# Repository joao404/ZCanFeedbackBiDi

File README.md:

# ZCanFeedbackBiDi
This project is based on the work of:
- Philipp Gathow (https://pgahtow.de/w/R%C3%BCckmeldung 8xRailCom-Detektor)
- Zimo Can Protocol

Several projects are include:
- Roco/Zimo CAN protocol to Z21 ethernet interface converter on ESP32
- Roco 10808 compatible Bidi/Railcom detector on ESP32 (currently suspended)
- Roco 10808 compatible Bidi/Railcom detector on STM32 using STM32Cube (currently suspended)
- Roco 10808 compatible Bidi/Railcom detector on STM32 using Arduino framework (ongoing. Planned to be finished on winter 2023)
- Roco 10808 compatible Bidi/Railcom detector on STM32 using Arduino framework and FreeRtos (ongoing. Planned to be finished on winter 2023)

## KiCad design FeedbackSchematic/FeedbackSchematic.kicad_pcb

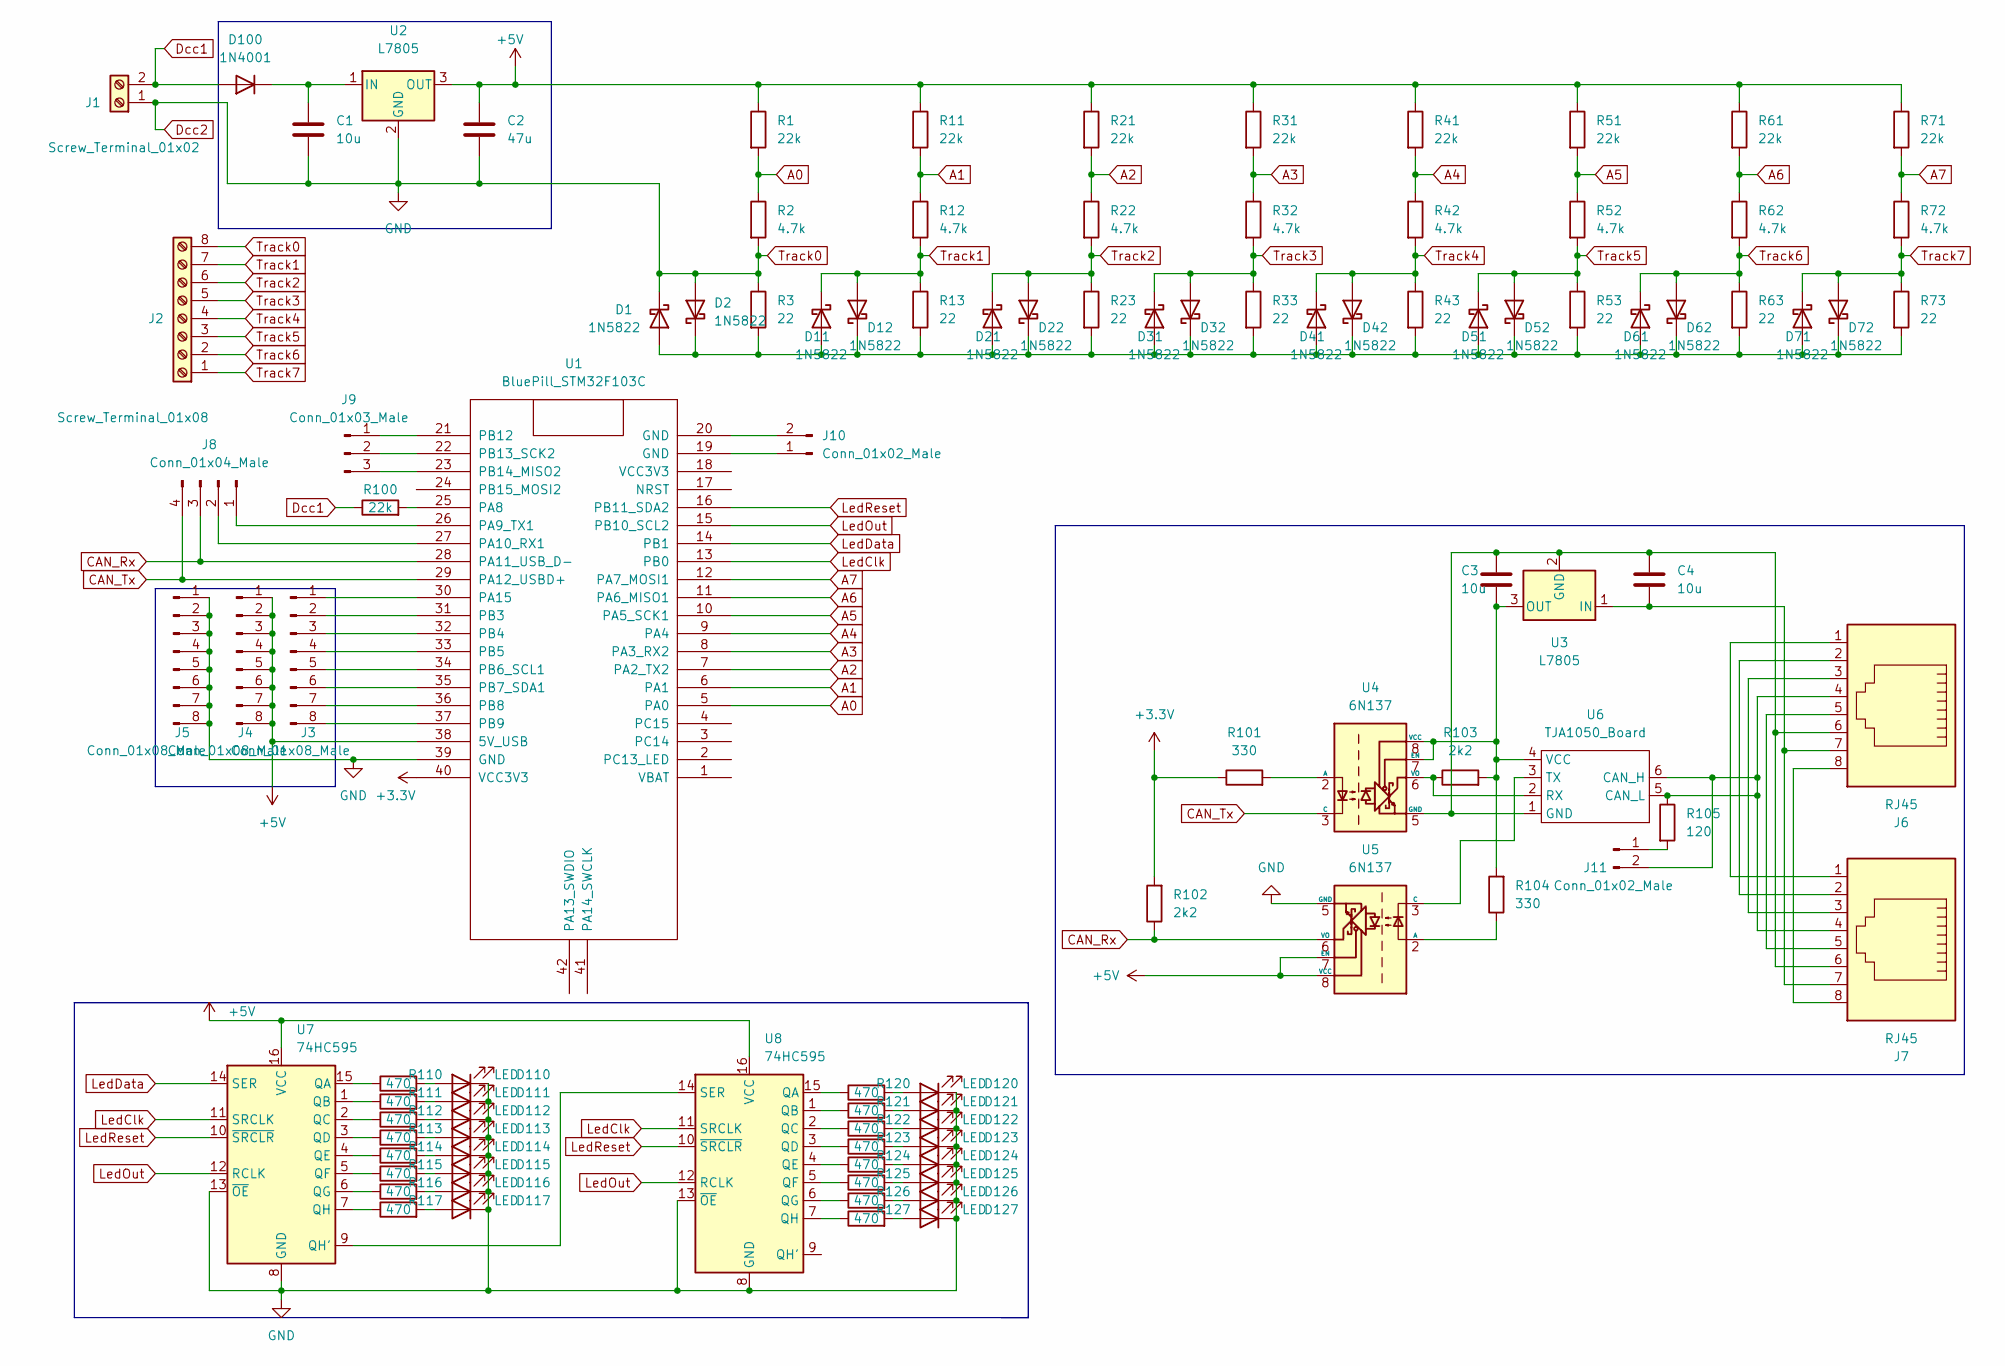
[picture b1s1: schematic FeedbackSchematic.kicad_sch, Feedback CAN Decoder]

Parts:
C1, C3, C4: 10u; CP_Radial_D5.0mm_P2.00mm
C2: 47u; CP_Radial_D5.0mm_P2.00mm
D1, D2, D11, D12, D21, D22, D31, D32, D41, D42, D51, D52, D61, D62, D71, D72: 1N5822; D_DO-201AD_P15.24mm_Horizontal
D100: 1N4001; D_DO-41_SOD81_P10.16mm_Horizontal
D110, D111, D112, D113, D114, D115, D116, D117, D120, D121, D122, D123, D124, D125, D126, D127: LED; LED_D3.0mm_Horizontal_O1.27mm_Z2.0mm
J1: Screw_Terminal_01x02; TerminalBlock_RND_205-00012_1x02_P5.00mm_Horizontal
J2: Screw_Terminal_01x08; TerminalBlock_RND_205-00018_1x08_P5.00mm_Horizontal
J3, J4, J5: Conn_01x08_Male; PinHeader_1x08_P2.54mm_Vertical
J6, J7: RJ45; RJ45_Amphenol_54602-x08_Horizontal
J8: Conn_01x04_Male; PinHeader_1x04_P2.54mm_Vertical
J9: Conn_01x03_Male; PinHeader_1x03_P2.54mm_Vertical
J10, J11: Conn_01x02_Male; PinHeader_1x02_P2.54mm_Vertical
R1, R11, R21, R31, R41, R51, R61, R71, R100: 22k; R_Axial_DIN0204_L3.6mm_D1.6mm_P5.08mm_Horizontal
R2, R12, R22, R32, R42, R52, R62, R72: 4.7k; R_Axial_DIN0204_L3.6mm_D1.6mm_P5.08mm_Horizontal
R3: 22; R_Axial_DIN0204_L3.6mm_D1.6mm_P5.08mm_Horizontal
R13, R23, R33, R43, R53, R63, R73: 22; R_Axial_DIN0204_L3.6mm_D1.6mm_P1.90mm_Vertical
R101, R104: 330; R_Axial_DIN0204_L3.6mm_D1.6mm_P5.08mm_Horizontal
R102, R103: 2k2; R_Axial_DIN0204_L3.6mm_D1.6mm_P5.08mm_Horizontal
R105: 120; R_Axial_DIN0204_L3.6mm_D1.6mm_P5.08mm_Horizontal
R110, R111, R112, R113, R114, R115, R116, R117, R120, R121, R122, R123, R124, R125, R126, R127: 470; R_Axial_DIN0204_L3.6mm_D1.6mm_P5.08mm_Horizontal
U1: BluePill_STM32F103C; Bluepill
U2, U3: L7805; TO-220-3_Vertical
U4, U5: 6N137; DIP-8_W7.62mm
U6: TJA1050_Board; TJA1050
U7, U8: 74HC595; DIP-14_W7.62mm_Socket

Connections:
+3.3V: R101.1, R102.2, U1.40 (VCC3V3)
+5V: C2.1, J4.1, J4.2, J4.3, J4.4, J4.5, J4.6, J4.7, J4.8, R1.1, R11.1, R21.1, R31.1, R41.1, R51.1, R61.1, R71.1, U1.38 (5V_USB), U2.3 (OUT), U5.7 (EN), U5.8 (VCC), U7.16 (VCC), U8.16 (VCC)
A0: R1.2, R2.1, U1.5 (PA0)
A1: R11.2, R12.1, U1.6 (PA1)
A2: R21.2, R22.1, U1.7 (PA2_TX2)
A3: R31.2, R32.1, U1.8 (PA3_RX2)
A4: R41.2, R42.1, U1.9 (PA4)
A5: R51.2, R52.1, U1.10 (PA5_SCK1)
A6: R61.2, R62.1, U1.11 (PA6_MISO1)
A7: R71.2, R72.1, U1.12 (PA7_MOSI1)
CAN_Rx: J8.3, R102.1, U1.28 (PA11_USB_D-), U5.6 (VO)
CAN_Tx: J8.4, U1.29 (PA12_USBD+), U4.3 (C)
Dcc1: D100.2 (A), J1.2, R100.1
Dcc2: C1.2, C2.2, D1.1 (K), D2.2 (A), D110.1 (K), D111.1 (K), D112.1 (K), D113.1 (K), D114.1 (K), D115.1 (K), D116.1 (K), D117.1 (K), D120.1 (K), D121.1 (K), D122.1 (K), D123.1 (K), D124.1 (K), D125.1 (K), D126.1 (K), D127.1 (K), J1.1, J2.8, J5.1, J5.2, J5.3, J5.4, J5.5, J5.6, J5.7, J5.8, R2.2, R3.1, U1.39 (GND), U2.2 (GND), U5.5 (GND), U7.8 (GND), U7.13 (~OE), U8.8 (GND), U8.13 (~OE)
LedClk: U1.13 (PB0), U7.11 (SRCLK), U8.11 (SRCLK)
LedData: U1.14 (PB1), U7.14 (SER)
LedOut: U1.15 (PB10_SCL2), U7.12 (RCLK), U8.12 (RCLK)
LedReset: U1.16 (PB11_SDA2), U7.10 (~SRCLR), U8.10 (~SRCLR)
unnamed: C1.1, D100.1 (K), U2.1 (IN)
unnamed: C3.1, R103.2, R104.2, U3.3 (OUT), U4.7 (EN), U4.8 (VCC), U6.4 (VCC)
unnamed: C3.2, C4.1, J6.6, J7.6, U3.2 (GND), U4.5 (GND), U6.1 (GND)
unnamed: C4.2, J6.7, J7.7, U3.1 (IN)
unnamed: D1.2 (A), D2.1 (K), D11.2 (A), D12.1 (K), D21.2 (A), D22.1 (K), D31.2 (A), D32.1 (K), D41.2 (A), D42.1 (K), D51.2 (A), D52.1 (K), D61.2 (A), D62.1 (K), D71.2 (A), D72.1 (K), R3.2, R13.2, R23.2, R33.2, R43.2, R53.2, R63.2, R73.2
unnamed: D110.2 (A), R110.2
unnamed: D111.2 (A), R111.2
unnamed: D112.2 (A), R112.2
unnamed: D113.2 (A), R113.2
unnamed: D114.2 (A), R114.2
unnamed: D115.2 (A), R115.2
unnamed: D116.2 (A), R116.2
unnamed: D117.2 (A), R117.2
unnamed: D120.2 (A), R120.2
unnamed: D121.2 (A), R121.2
unnamed: D122.2 (A), R122.2
unnamed: D123.2 (A), R123.2
unnamed: D124.2 (A), R124.2
unnamed: D125.2 (A), R125.2
unnamed: D126.2 (A), R126.2
unnamed: D127.2 (A), R127.2
unnamed: J3.1, U1.30 (PA15)
unnamed: J3.2, U1.31 (PB3)
unnamed: J3.3, U1.32 (PB4)
unnamed: J3.4, U1.33 (PB5)
unnamed: J3.5, U1.34 (PB6_SCL1)
unnamed: J3.6, U1.35 (PB7_SDA1)
unnamed: J3.7, U1.36 (PB8)
unnamed: J3.8, U1.37 (PB9)
unnamed: J6.1, J7.1
unnamed: J6.2, J7.2
unnamed: J6.3, J7.3
unnamed: J6.5, J7.5
unnamed: J6.8, J7.8
unnamed: J8.1, U1.26 (PA9_TX1)
unnamed: J8.2, U1.27 (PA10_RX1)
unnamed: J9.1, U1.21 (PB12)
unnamed: J9.2, U1.22 (PB13_SCK2)
unnamed: J9.3, U1.23 (PB14_MISO2)
unnamed: J10.1, U1.19 (GND)
unnamed: J10.2, U1.20 (GND)
unnamed: J11.1, R105.2
unnamed: J6.4, J7.4, J11.2, R105.1, U6.5 (CAN_L), U6.6 (CAN_H)
unnamed: R100.2, U1.25 (PA8)
unnamed: R101.2, U4.2 (A)
unnamed: R103.1, U4.6 (VO), U6.2 (RX)
unnamed: R104.1, U5.2 (A)
unnamed: R110.1, U7.15 (QA)
unnamed: R111.1, U7.1 (QB)
unnamed: R112.1, U7.2 (QC)
unnamed: R113.1, U7.3 (QD)
unnamed: R114.1, U7.4 (QE)
unnamed: R115.1, U7.5 (QF)
unnamed: R116.1, U7.6 (QG)
unnamed: R117.1, U7.7 (QH)
unnamed: R120.1, U8.15 (QA)
unnamed: R121.1, U8.1 (QB)
unnamed: R122.1, U8.2 (QC)
unnamed: R123.1, U8.3 (QD)
unnamed: R124.1, U8.4 (QE)
unnamed: R125.1, U8.5 (QF)
unnamed: R126.1, U8.6 (QG)
unnamed: R127.1, U8.7 (QH)
unnamed: U5.3 (C), U6.3 (TX)
unnamed: U7.9 (QH'), U8.14 (SER)
Track1: D11.1 (K), D12.2 (A), J2.7, R12.2, R13.1
Track2: D21.1 (K), D22.2 (A), J2.6, R22.2, R23.1
Track3: D31.1 (K), D32.2 (A), J2.5, R32.2, R33.1
Track4: D41.1 (K), D42.2 (A), J2.4, R42.2, R43.1
Track5: D51.1 (K), D52.2 (A), J2.3, R52.2, R53.1
Track6: D61.1 (K), D62.2 (A), J2.2, R62.2, R63.1
Track7: D71.1 (K), D72.2 (A), J2.1, R72.2, R73.1

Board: 2 copper layers, 102 parts (0 on the bottom side), 88 nets, no tracks yet.

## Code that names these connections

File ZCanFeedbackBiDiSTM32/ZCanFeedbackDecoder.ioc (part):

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Mcu.Name=STM32F103C(8-B)Tx
Mcu.Package=LQFP48
Mcu.UserName=STM32F103C8Tx
PA0-WKUP.GPIOParameters=GPIO_Label
PA0-WKUP.GPIO_Label=Track1
PA0-WKUP.Signal=ADCx_IN0
PA1.GPIOParameters=GPIO_Label
PA1.GPIO_Label=Track2
PA1.Signal=ADCx_IN1
PA10.GPIOParameters=GPIO_Label
PA10.GPIO_Label=usartRx
PA10.Mode=Asynchronous
PA10.Signal=USART1_RX
PA11.GPIOParameters=GPIO_Label
PA11.GPIO_Label=canRx
PA11.Mode=CAN_Activate
PA11.Signal=CAN_RX
PA12.GPIOParameters=GPIO_Label
PA12.GPIO_Label=canTx
PA12.Mode=CAN_Activate
PA12.Signal=CAN_TX
PA2.GPIOParameters=GPIO_Label
PA2.GPIO_Label=Track3
PA2.Signal=ADCx_IN2
PA3.GPIOParameters=GPIO_Label
PA3.GPIO_Label=Track4
PA3.Signal=ADCx_IN3
PA4.GPIOParameters=GPIO_Label
PA4.GPIO_Label=Track5
PA4.Signal=ADCx_IN4
PA5.GPIOParameters=GPIO_Label
PA5.GPIO_Label=Track6
PA5.Signal=ADCx_IN5
PA6.GPIOParameters=GPIO_Label
PA6.GPIO_Label=Track7
PA6.Signal=ADCx_IN6
PA7.GPIOParameters=GPIO_Label
PA7.GPIO_Label=Track8
PA7.Signal=ADCx_IN7
PA8.GPIOParameters=GPIO_Label,GPIO_ModeDefaultEXTI
PA8.GPIO_Label=dccInput
PA8.GPIO_ModeDefaultEXTI=GPIO_MODE_IT_RISING_FALLING
PA8.Signal=GPXTI8
PA9.GPIOParameters=GPIO_Label
PA9.GPIO_Label=usartTx
PA9.Mode=Asynchronous
PA9.Signal=USART1_TX
PB0.GPIOParameters=GPIO_PuPd,GPIO_Label
PB0.GPIO_Label=configRailcom
PB0.GPIO_PuPd=GPIO_PULLUP
PB0.Signal=GPIO_Input
PB1.GPIOParameters=GPIO_PuPd,GPIO_Label
PB1.GPIO_Label=configNetworkId
PB1.GPIO_PuPd=GPIO_PULLUP
PB1.Signal=GPIO_Input
PC13-TAMPER-RTC.GPIOParameters=GPIO_Label
PC13-TAMPER-RTC.GPIO_Label=LED_BUILTIN
PC13-TAMPER-RTC.Signal=GPIO_Output
PD0-OSC_IN.Mode=HSE-External-Oscillator
PD0-OSC_IN.Signal=RCC_OSC_IN
PD1-OSC_OUT.Mode=HSE-External-Oscillator
PD1-OSC_OUT.Signal=RCC_OSC_OUT
RCC.SYSCLKFreq_VALUE=72000000
RCC.SYSCLKSource=RCC_SYSCLKSOURCE_PLLCLK
board=custom

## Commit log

2022-09-14 Initial Checkin
2022-09-17 Additional callbacks and preparation for 10808
2022-09-24 ZCan working as feedback. Not tested
2022-09-24 Optimizing adress reporting
2022-09-24 Added function for id programming with button and second feedback decoder handling
2022-09-26 Fixed errors when using at Z21
2022-09-26 Added handling of Module Power Info telegram
2022-10-04 separate for ESP32 and STM32
2022-10-04 deleted old files
2022-10-05 Added simple detector function
2022-10-07 Fixed can message receiving
2022-10-07 Bugfixes
2022-10-07 Bugfix for Esp32
2022-10-08 Stm32 support step1
2022-10-08 Stm32 compilable without DCC and Railcom
2022-10-12 CAN functioning for STM32
2022-10-16 Added dcc function
2022-10-17 DCC not functioning, first steps for Railcom
2022-10-18 Changed to Stm32duino
2022-10-20 Adapted eXoCan
2022-10-20 can driver uses all 3 mailboxes
2022-10-20 Move flash to extra class
2022-10-23 Fix of Flash, reading Railcomdata
2022-10-24 Restructuring
2022-10-25 Railcom Step 2 and Current Sense detection
2022-10-27 Railcom functioning step3
2022-10-27 New coding guideline
2022-10-31 railcom functioning without direction detection
2022-11-01 refactoring
2022-11-01 Railcomrefactor, channel 2 detection and direction detection
2022-11-04 Railcom channel detection correction
2022-11-11 Fixed errors
2022-11-11 Fixed detection reporting
2022-11-12 changed input parameter order
2022-11-15 Z21 server compilable. No function yet
2022-11-16 Additional ZCan cases
2022-11-16 CanDetector handling, untested
2022-11-30 Bugfix
2022-12-05 Updated observer pattern
2022-12-09 Station and Feedback Running
2022-12-10 Deactivate Debugging
2022-12-13 Fix udp bufferoverflow
2022-12-13 Added base for schematic
2022-12-19 invert pin read and finish schematic
2022-12-26 Added decoder function for servos etc.
2022-12-26 Fix reporting of config values bug
2022-12-27 Config dcc address for function decoder and status led
2022-12-27 Bugfix in case of two feedback signals
2022-12-27 Updated schematics
2022-12-29 Added footprints except tja1050
2023-01-01 Updated footprint
2023-01-02 Added cyclic status led call
2023-01-29 Railcom Debugging
2023-09-05 Adapted readme and added code comments
2023-09-11 First changes for stable railcom reading(untested)
2023-09-14 Railcom improvement (not working yet)
2023-09-15 Railcom working but channel 1 detection not stable
2023-09-22 Railcom and current sense based on DMA
2023-09-24 Added support for DCC output with railcom
2023-09-24 Updated step and mode config
2023-09-25 Increased Preamble in DCC library and fix compiler warning
2023-09-25 Handling of comming and going railcom loco
2023-09-26 Refactoring railcom part 1
2023-09-26 Refactoring railcom part 2
2023-09-26 Refactoring railcom part 3
2023-09-28 Railcom working again
2023-09-29 Handling printfunc == nullptr
2023-09-29 Stm32f1 abstraction layer for railcom
2023-10-08 First preparation for mob and stat railcom cmd
2023-10-08 Preparation for railcom cmd type
2023-10-29 Added Shortcircuit detection
2023-10-29 Switch to mA and report current
2023-11-01 Latest changes railcom and pcb
2023-11-19 Lattest changes for dcc generation
2023-11-20 Start freertos development
2023-11-22 Add loco delete function for station and fix memory error
2023-11-25 Add fifo with fixed size
2023-11-25 Tested Fifo
2023-11-26 Making FreeRtos work
2023-11-26 FiFo changes also for non FreeRtos
2023-11-28 Correct block analysis for empty block
2023-11-29 Stabilize track detection
2023-11-30 Changed railcom reporting
